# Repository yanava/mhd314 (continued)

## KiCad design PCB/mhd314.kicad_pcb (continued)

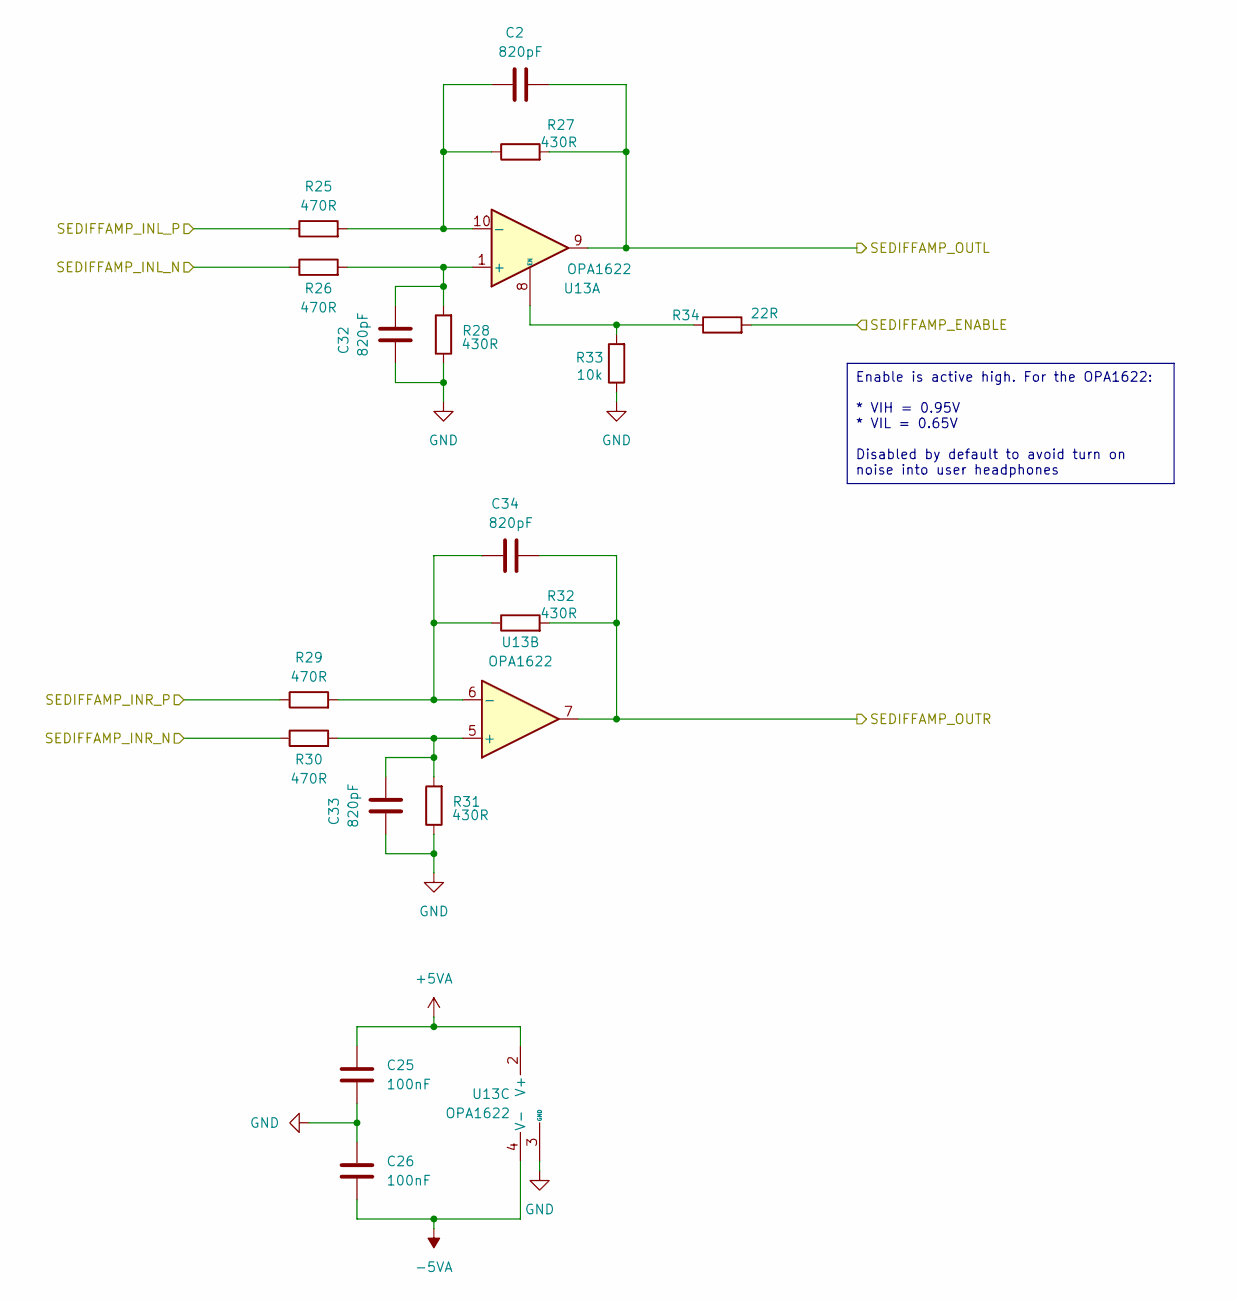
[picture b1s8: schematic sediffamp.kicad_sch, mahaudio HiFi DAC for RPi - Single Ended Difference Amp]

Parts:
C2, C32, C33, C34: 820pF; C_0603_1608Metric_Pad1.08x0.95mm_HandSolder; Tolerance 10%; Voltage 50V; JLCPCB Part # C99081
C25, C26: 100nF; C_0402_1005Metric_Pad0.74x0.62mm_HandSolder; Tolerance 10%; Voltage 16V; JLCPCB Part # C1525
R25, R26, R29, R30: 470R; R_0402_1005Metric_Pad0.72x0.64mm_HandSolder; Tolerance 0.1%; JLCPCB Part # C445590
R27, R28, R31, R32: 430R; R_0402_1005Metric_Pad0.72x0.64mm_HandSolder; Tolerance 0.1%; JLCPCB Part # C186317
R33: 10k; R_0402_1005Metric_Pad0.72x0.64mm_HandSolder; Tolerance 5%; JLCPCB Part # C25744
R34: 22R; R_0402_1005Metric_Pad0.72x0.64mm_HandSolder; Tolerance 5%; JLCPCB Part # C25092
U13: OPA1622; Texas_S-PVSON-N10; JLCPCB Part # C2876559

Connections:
+5VA: C25.1, U13.2 (V+); also elsewhere on the board
-5VA: C26.2, U13.4 (V-), U13.11 (V-); also elsewhere on the board
/AMP/BalDiffAmp_L/BALDIFFAMP_IN_N: R26.1; also elsewhere on the board
/AMP/BalDiffAmp_L/BALDIFFAMP_IN_P: R25.1; also elsewhere on the board
/AMP/BalDiffAmp_R/BALDIFFAMP_IN_N: R30.1; also elsewhere on the board
/AMP/BalDiffAmp_R/BALDIFFAMP_IN_P: R29.1; also elsewhere on the board
/AMP_SE_EN: R34.2; also elsewhere on the board
/OUT_SE_L: C2.2, R27.2, U13.9; also elsewhere on the board
/OUT_SE_R: C34.2, R32.2, U13.7; also elsewhere on the board
GND: C25.2, C26.1, C32.1, C33.1, R28.1, R31.1, R33.1, U13.3 (GND); also elsewhere on the board
unnamed: C32.2, R26.2, R28.2, U13.1 (+)
unnamed: C2.1, R25.2, R27.1, U13.10 (-)
unnamed: R33.2, R34.1, U13.8 (EN)
unnamed: C33.2, R30.2, R31.2, U13.5 (+)
unnamed: C34.1, R29.2, R32.1, U13.6 (-)

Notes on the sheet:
Enable is active high. For the OPA1622: * VIH = 0.95V * VIL = 0.65V Disabled by default to avoid turn on noise into user headphones

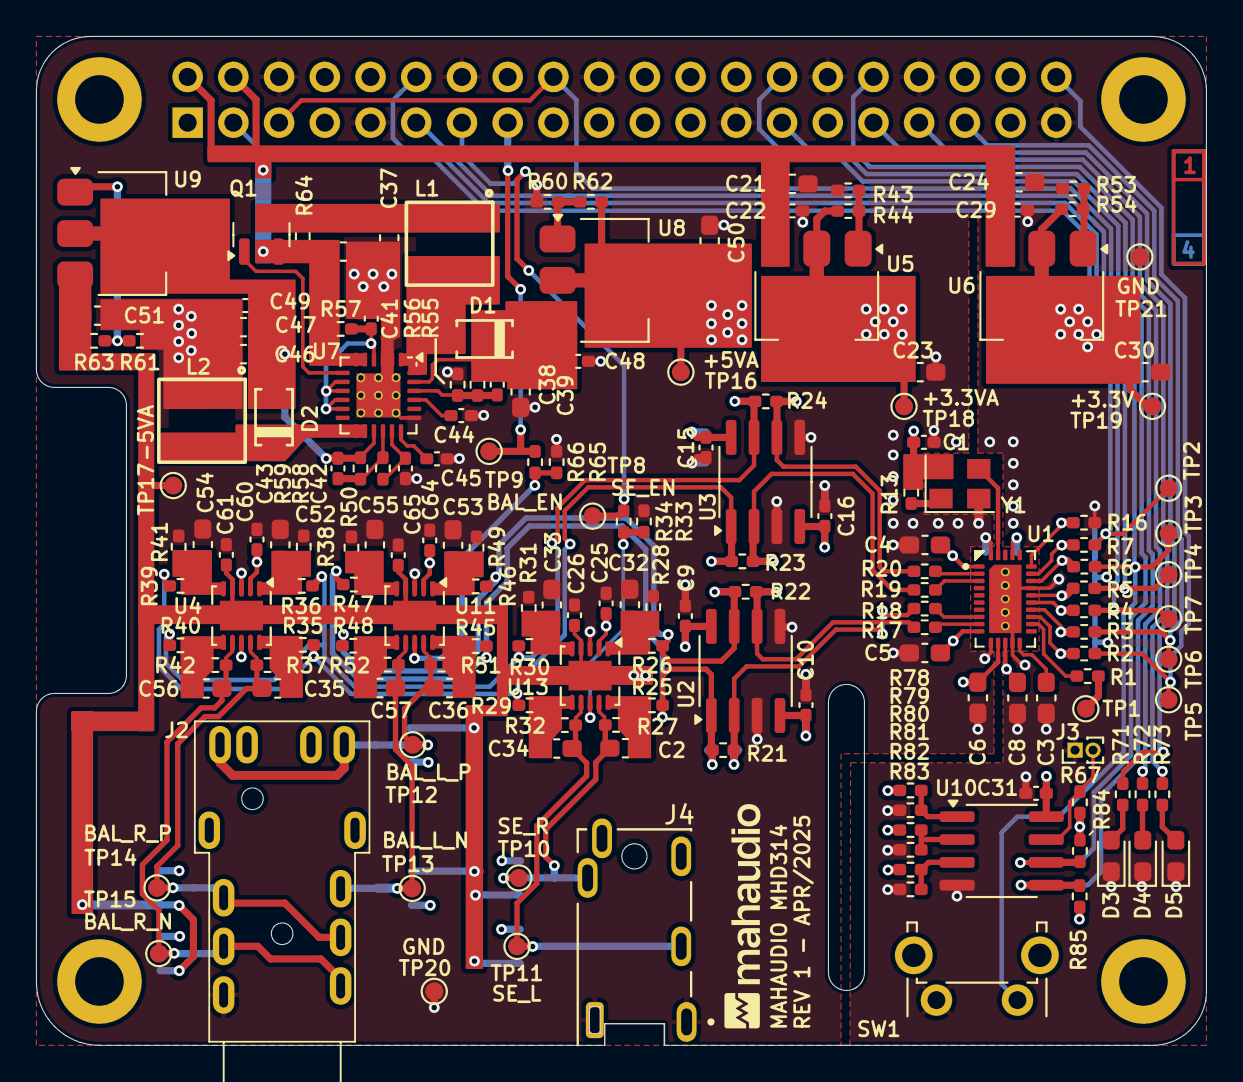
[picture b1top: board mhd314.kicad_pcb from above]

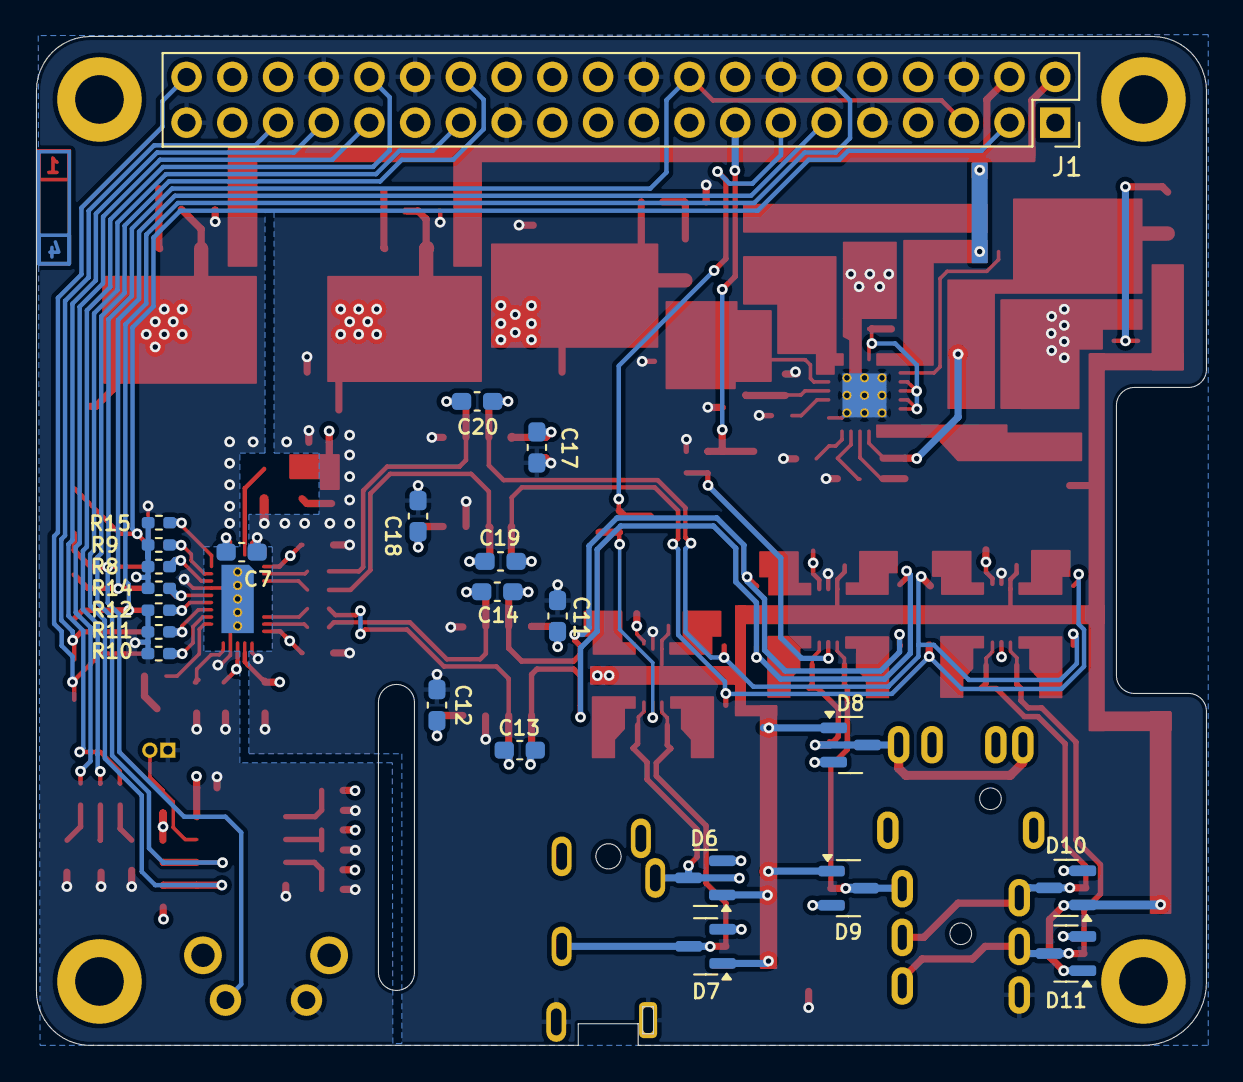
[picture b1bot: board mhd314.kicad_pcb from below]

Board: 4 copper layers, 65.0 x 56.1 mm, 194 parts (23 on the bottom side), 86 nets.

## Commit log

2024-08-01 Added presentations under Documentation
2024-08-15 Added PCB project with DAC module
2024-08-15 Added Live 08 Presentation
2024-08-28 Finalized DAC and made it a module. Added Live 09 presentation
2024-09-04 Updated dac schematics and added simulations. Updated until Live 11
2024-09-19 Added AMP stage circuits. Updated until Live 13
2024-10-31 Added power supply and adjusted the AMP section to use only OPA1622 as output amp. In sync with Live 16
2024-10-31 Added presentations until live 16
2024-10-31 Added WE inductor for power. Library is attached to project for reference
2024-12-04 Added connectors
2024-12-16 Added E2P and testpoints
2024-12-19 PCB drawn with connector placement ok
2025-01-09 Started placement, current with Live 20
2025-01-22 Finished basic placement
2025-02-05 Routed power section
2025-02-07 Routed DAC section
2025-02-21 Routed single ended path and moved some components to top side
2025-02-25 Advances all basic track routing. Pending power planes, grounding and optimization
2025-02-27 Basic routing finished. Still missing some optimizing steps and DRC
2025-03-05 Routing revised, added some missing parameters to components
2025-03-05 Added a few more parameters
2025-03-06 Updated PCB with digital traxce suggestions. Added JLCPCB Pns
2025-03-06 Updates some DNPs on PCB
2025-03-06 gitignore
2025-03-08 Changed the 4.4mm connector and fixed a bunch o library related problems
2025-03-12 Increased trace width and clearance to 0.15mm. Changed the Pentaconn connector to JLCPCB supported part from GSwitch
2025-03-13 Changed resistor values to match JLCPCB + general board revision
2025-03-17 Added filter capacitors to OPA1622 circuitry
2025-03-17 Improved silk screen positioning and optimized some of the tracks
2025-03-18 Optimized designator positions and DNP for capacitors in OPA1622
2025-03-18 Redone placement and layout of OPA1622. Still finishing touches
2025-03-19 Finished routing with new OPA1622 layout. Pending review of designators.
2025-03-19 Optimized tracks and designators
2025-03-19 Changed the BOM field for JLCPCB to the original name instead of LCSC
2025-03-20 Changed single ended connector for gold plated part and changed resistor and capacitor values of opa1622 amp for improved power on high impedance headphones
2025-04-15 Changes in E2P for better identification of the board
2025-04-16 Updated inductor to improve production
2025-04-16 Added courtyard information on Inductor
